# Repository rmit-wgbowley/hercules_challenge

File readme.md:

<!--
Color Palette:
- #F3F4F4
- #0DFDF7
-->

<p align="center">
  
  <br>
  <em>Axial Shake Powered Pill System – Electromechanical Design of the IsoPod by <a href="https://github.com/wgbowley">William Bowley</a></em>
</p>

--- 
The Hercules Challenge is a co-design consortium challenge available to first-semester, first-year engineers through the mandatory introductory class, "Introduction to Professional Engineering."

> [!IMPORTANT]
> `The Pantheon` consortium received a commendation award for their work on the `IsoPod` at the Hercules Challenge night at RMIT.

---

TLDR: Designed, simulated, manufactured, and experimentally validated a human-powered axial electromagnetic generator producing `0.43–0.47 W` from hand shaking using custom FEA and physical prototype testing

# Overview

The `IsoPod` is a pill system that reminds users when to take their medication through an e-ink display on the cylindrical face of the device, providing a simple visual reminder.

This repository focuses on the design, simulation, construction, and validation of the `axial shake generator` (ASG) at the device's core. The generator converts intentional shaking motion into electrical energy via magnetic induction, which charges the IsoPod's Li-Po battery. This extends battery life, or with enough motion, can enable complete self-reliance.

> [!Important]
> **Measured Output (8.8 Hz human shaking):**
> - Peak Voltage: `16.8 V`
> - RMS Voltage: `3.47 V`
> - Power Output: `0.43–0.47 W`

> [!Important]
> The generator has not been tested with a charging load nor power management system. Power output is expected to decrease, but the magnitude is unknown.

### Why generate electrical?

In humanitarian contexts, reliable grid power isn't guaranteed, nor are reliable supply chains for expendable batteries. The ASG decouples the `IsoPod` from external infrastructure by converting user motion into electrical 
energy.

### Table of Contents

- [Overview](#overview)
- [Why generate electrical?](#why-generate-electrical)
- [Axial Shake Generator](#axial-shake-generator)
  - [Electromagnetics](#electromagnetics)
  - [Design & Topology](#design--topology)
  - [Numerical Model](#numerical-model)
  - [Simulation Results](#simulation-results)
- [Construction](#construction)
- [Results](#results)
- [Validation](#validation)
  - [New Mechanical Model](#new-mechanical-model)
  - [Simulation Results](#simulation-results-1)
- [Conclusion](#conclusion)
- [Bibtex Citation](#bibtex-citation)

# Axial Shake Generator

<div align="center">
  
  <p><i>Figure 1: Cross-sectional analysis: <a href="02_fabrication/readme.md">Click here for CAD files</a></i></p>
</div>

The generator consists of an armature `(greyish-olive)` made of poles (magnets), a stator `(minty aqua)` made of slots (coils), and restoring magnets `(light yellow-green)` which act as magnetic springs that allow the armature to build velocity from the user shaking the device with their forearm muscles.

## Electromagnetics

An ASG produces electricity via the interaction between a slot and a pole. When a pole moves axially through a slot, it produces an induced voltage within that slot due to the changing magnetic field generating a changing electric field. The induced electric field opposes the change in magnetic flux that produced it, a consequence of Lenz's law. These ideas come together to form `Faraday's Law of Induction`:

$$V = -N\frac{d\Phi}{dt} \implies -\frac{d\lambda}{dt}$$

where $λ = N\Phi$ is the flux linkage between the slot and pole. Flux linkage can be thought of as the magnitude of how strongly the magnetic field links with the winding (turns in a slot). Higher linkage generally means the system can produce a larger induced voltage for the same change in armature position.

Luckily, using related rates, the two main parameters appear:

$$V_{\text{induced}} = -\frac{d\lambda}{dt} \implies -\frac{d\lambda}{dz} \cdot \frac{dz}{dt}$$

The first term is the derivative of flux linkage over the z-axis (magnetic design), and the second term is the z-axis velocity (mechanical input). These can be analytically approximated as:

> [!important]
> Flux linkage can be approximated analytically for intuition. The final flux linkage was obtained using Finite Element Analysis (FEA).

$$\frac{dz}{dt} = A \omega \cos(\omega t + \phi)$$
$$\frac{d\lambda}{dz} = \frac{d}{dz} (B \cos(kz)) \implies -\mu H k \sin(kz)$$

> [!note]
> For a simple magnetic circuit, magnetic flux density can be related to magnetic field strength by `B = μH`, where `B` is the magnetic flux density, `H` is the magnetic field intensity, and `μ` is the permeability, the ability of a material to support magnetic flux.

where `k = 2π / pitch` is the spatial frequency.

These two derivatives expose the important mechanics of the system. Increasing acceleration `A` and frequency `ω` may increase induced voltage, but these are constrained by the user's physical abilities. Whereas the permeability `μ` and `H` may increase the induced voltage while generally not being constrained by the user's physical abilities.

Once induced voltage is established, the usable electrical power is determined by the generator's internal resistance:

$$P = \frac{V_{\text{rms}}^2}{R_{\text{internal}}}$$

This relationship drives one of the main trade-offs: increasing turns raises induced voltage but also increases resistance due to longer wire length. The optimal design maximizes `V/R`, not just peak voltage.

> [!important]
> The generator design was constrained by the IsoPod system requirements:
> - Cylindrical form factor: radial thickness < `12.5 mm`, height < `250 mm`
> - Human-powered input motion (reasonable frequency and acceleration)
> - Low-maintenance energy harvesting
> - Easy to construct with basic tools

## Design & Topology

<div align="center">
  
  <p><i>Figure 2: High level electrical machine topology</i></p>
</div>

> [!note]
> `N-S` represents an axially magnetized permanent magnet pole. `PA` represents phase A, where `PA+` and `PA-` indicate opposite winding directions.

The high-level topology in figure 2 was selected to enable oscillatory motion through magnetic restoring forces. The end poles act as magnetic springs, creating a restoring force when the armature approaches the limits of travel.

The alternating pole arrangement (`N-S|S-N`) was selected because the transition between opposing poles creates a rapid change in magnetic field along the z-axis, increasing the spatial rate of change of flux linkage:

$$V \propto \frac{d\lambda}{dz}$$

A pole pitch of `10 mm` was selected, matching the pole length and maintaining direct magnetic coupling between adjacent opposing poles. The topology uses four stator slots interacting with four active armature poles, with two additional poles placed on each end of the armature to increase usable travel distance. This allows approximately `20 mm` of positive and negative armature displacement while maintaining magnetic coupling between the armature and stator.

Maintaining slot overlap throughout the motion range produces a more consistent induced voltage waveform, where the primary amplitude is dominated by the mechanical velocity term:

$$V \propto \frac{dz}{dt}$$

The symmetric pole arrangement also reduces unwanted harmonic content compared with asymmetric topologies. Finally, no high-permeability materials were introduced into the armature or stator structure. The stator consists of copper windings, while the magnetic poles use `N52 Neodymium` permanent magnets.

Given the 4 slots within the stator and the 8 poles within the armature, the measured frequency relationship suggests:

$$f_{\text{electrical}} \approx 4 \times f_{\text{mechanical}}$$

This is consistent with the pole pitch and the number of magnetic cycles encountered per mechanical oscillation.

## Numerical Model

> [!important]
> This area is recommended for individuals more familiar with electromagnetic finite element simulations.

The ASG was modelled using `FemmMagneticRender` (FEMM) with `shapely` for translating `PYFEA` CSG (constructive solid geometry) to FEMM native primitives. An axially symmetric coordinate system (z-r) was used due to the generator's rotational symmetry around its z-axis. A Dirichlet boundary condition was applied, with the radial boundary at `2×` the slot outer radius and the axial boundary at `1.2×` the stator tube length. The armature motion relative to the origin was simulated using:

$$ z = \text{travel} \cdot \sin(2\pi f t) $$

The resistance was obtained from `FemmMagneticSolver` during an initial configuration solve, and then the flux linkage was obtained per solve. Using the simulation time-step, the induced voltage was calculated using finite difference:

$$V_{\text{induced}} = -\frac{\lambda_{\text{new}} - \lambda_{\text{old}}}{t_{\text{step}}}$$

This was then used to calculate the RMS voltage, and using the generator's internal resistance, the expected power output was obtained. This method represents a `quasi-transient` method due to its use of asymptotic field conditions ($t=\infty$) per time step. This is reasonable due to the absence of highly magnetically permeable materials and the low operating frequency of the generator.

## Simulation Results

> [!IMPORTANT]
> The model was configured with the following parameters:
> - Temperature: `293.15 K`, Time step: `1ms`
> - Mechanical Shaking Frequency: `8.81 Hz`, Electrical Shaking Frequency: `35.2 Hz`
> - peak-to-peak travel: `40 mm`
> - Pole Coercivity: `956 kA/m`, Pole Permeability: `1.05 ∅`
> - Slot Conductivity: `60.07 MS/m`, Slot Permeability: `1.0 ∅`, Fill Factor: `0.47 ∅`, Turns: `184`

<div align="center">
  
  <p><i>Figure 3: Simulated static |B| along the z-axis of the generator</i></p>
</div>

> [!IMPORTANT]
> The quasi-transient simulation predicted:
> - Time: `0.228 s`, Time steps: `228`
> - Peak voltage: `5.161 V`, RMS Voltage: `2.696 V` 
> - Positive Rate: `486.06 V/s`, Negative Rate: `-844.25 V/s`
> - Resistance: `22.54 Ω`, Power: `0.323 W` 

<div align="center">
  
  <p><i>Figure 4: Simulated induced voltage vs time and position vs time</i></p>
</div>

The parameter file can be found [here](01_simulation/01_simple_motion/parameters.uiv), written in `.uiv` (unit-informed values). The simulation files can be found [here](01_simulation/readme.md), written in Python using the `pyfea` solver-adapter engine. Solver assumptions can be found [here](03_data/assumptions_printout.md).

## Construction

The generator was printed out of ABS on a Voron 2.4. The armature consisted of a carbon fibre rod with `8` x `N52` poles inserted into it in the pattern described above, using superglue to secure the end poles.

The stator consisted of `4` coils with `180` turns per coil of `0.2 mm` enameled copper wire, with each coil wound in the opposite direction to the last as described above. The coils were secured in place with `10 mm` and `5 mm` thick Kapton tape, with the first and last layers of the coil being wrapped.

The restoring magnets were flat `12 mm x 3 mm` neodymium magnets. The generator stator was split into two pieces: the main piece, which housed the coils and one restoring magnet, and the cap, which held the other restoring magnet and was attached via `3` x `M3 x 20 mm` bolts. The two outputs of the generator were secured to the side and then extended with `~1.25 mm` stranded copper wire.

<div align="center">
  
  <p><i>Figure 5: Side profile (Construction)</i></p>
</div>

## Results

The completed generator was tested by hand-shaking at a measured fundamental mechanical frequency of `8.81 Hz` with an electrical frequency of `35.2 Hz`
(the 4 coils produce 4 cycles per mechanical oscillation). The open-circuit voltage was recorded using an oscilloscope:

> [!IMPORTANT]
> The oscilloscope measurements:
> - Positive Peak: `16.8 V`, Negative Peak: `-16.4 V`
> - Positive Rate: `131 V/s`, Negative Rate: `-246 V/s` (Slew Rate)
> - V_RMS(AV): `3.47 V`, V_RMS(PEAK): `3.63 V`
> - Resistance: `27.8 Ω`, Power: `0.43-0.47 W`

> [!NOTE]
> Slew rate can be affected by probe loading due to parasitic capacitance and inductance. Hence `dv/dt` may be slowed due to the `RLC` circuit formed.

<div align="center">
  
  <p><i>Figure 6: Voltage vs time trace @ 10V/div vertical, 50ms/div horizontal</i></p>
</div>

The measured waveform shown in Figure 6 has a similar shape to the predicted waveform in Figure 4 but seems less periodic and more jerky. Another observation is that the negative recovery appears stretched while still being a similar amplitude. This is most likely attributed to degradation of the prototype due to its usage as a demo item.

# Validation

The simulated power output was `0.323 W` whereas the measured power was `0.43-0.47 W`, which is `25-45%` lower than the measured value. The peak voltages are much higher and the slew rate was significantly different, leading to the possible source being the idealized motion of the armature versus the realized motion.

The simulation used the same mechanical frequency but produced lower peak voltages. If the prototype's armature acceleration was much higher than expected, the armature was likely slamming into the end-caps due to the repulsion force not being high enough. The maximum velocity was most likely higher and hence:

$$V \propto \frac{d\lambda}{dz}$$

## New Mechanical Model

> [!important]
> This area is recommended for individuals more familiar with electromagnetic finite element simulations.

Given this, a new model for the motion could be proposed that takes into consideration the magnetic repulsion force and the likely much higher mechanical acceleration but lower frequency, using an oscillating force function:

$$F_{\text{magnetic}} = -\frac{dU}{dz}$$
$$F_{\text{shaking}} = am\sin(\omega t + \phi)$$

One approach would be to model the armature velocity as:

$$\frac{dz}{dt} = \int \frac{F_{\text{magnetic}} + F_{\text{shaking}}}{m} \ dt$$

> [!Note]
> Euler method was used to integrate from acceleration to z-position, the stability was not formalized.

However, given the ability of `FemmMagneticSolver` to calculate the Maxwell stress tensor, the $F_{\text{magnetic}}$ term was obtained directly from the solver rather than using finite difference of the magnetic energy density over the z-axis. This decouples the solution from the displacement output, removing dynamic step sizes and leading to a potentially more stable solution.

## Simulation Results 

> [!IMPORTANT]
> The model was configured with the following parameters:
> - Temperature: `293.15 K`, Time step: `1 ms`
> - Mechanical Shaking Frequency: `8.8 Hz`, Electrical Shaking Frequency: `35.2 Hz`
> - Acceleration: `100 m/s²`, peak-to-peak travel: `40 mm`
> - Pole Coercivity: `956 kA/m`, Pole Permeability: `1.05 ∅`
> - Slot Conductivity: `60.07 MS/m`, Slot Permeability: `1.0 ∅`, Fill Factor: `0.47 ∅`, Turns: `184`

> [!IMPORTANT]
> The quasi-transient simulation predicted:
> - Time: `0.228 s`, Time steps: `228`
> - Peak voltage: `12.35 V`, RMS Voltage: `3.44 V` 
> - Positive Rate: `634.76 V/s`, Negative Rate: `-2.32 kV/s`
> - Resistance: `22.54 Ω`, Power: `0.526 W` 

<div align="center">
  
  <p><i>Figure 7: New simulation results (Simulation Results)</i></p>
</div>

The parameter file can be found [here](01_simulation/02_advance_motion/parameters.uiv), written in `.uiv` (unit-informed values). The simulation files can be found [here](01_simulation/readme.md), written in Python using the `pyfea` solver-adapter engine. Solver assumptions can be found [here](03_data/assumptions_printout.md).

# Conclusion

The axial shake generator successfully produced `0.43-0.47 W` of usable power from human motion at a mechanical frequency of `8.8 Hz` (electrical `35.2 Hz`) with an unknown acceleration function. The simulation with the new mechanical model predicted `0.526 W`, within `12-22%` of measured values. The differences in slew rates between the simulation and measured results can be attributed to no-load electrical dynamics versus the oscilloscope probe loading.

> [!IMPORTANT]
> Key Takeaways:
> - The `N-S|S-N` magnet topology effectively increases `dλ/dz`, producing sharp B-field spikes
> - The mechanical model incorporating boundary clamping and Maxwell stress tensor produces a waveform shape much closer to reality than the ideal sinusoidal model
> - The quasi-transient model using a hybrid force function predicted power within `22%`; however, acceleration needs validation
> - The `180` turn prototype produced `16.8 V` peaks, which is sufficient for the IsoPod's target applications

> [!TIP]
> Future work should focus on:
> - Using a shaking apparatus for repeatable external motion paths that could be fed into the simulation
> - Improving fill factor to decrease generator size or increase the number of turns within the generator's form factor
> - Validating the computational model across more generator parameters and pole-slot factors
> - Investigating whether the end-cap magnets improve energy output or reduce it
> - Investigating efficient methods of converting electrical energy into stored energy
> - Investigating the effect of the probe's `RLC` circuit or generator conversion circuit on dynamics

The generator design demonstrated the feasibility of powering low-energy devices in humanitarian contexts where grid power is unreliable, depending on load factors. However, it may be more viable as a battery supplementary system, depending on the trade-offs between battery size and generator duty cycle.

### Bibtex Citation:

```
@misc{Bowley_2024,
  author = {Bowley, William},
  title = {{IsoPod: Axial Shake Generator}},
  url = {https://github.com/rmit-wgbowley/isopod-generator},
  year = {2024},
  note = {
    GitHub repository,
    Electromagnetic Subsystem Of The Isopod
  },
  license = {MIT}
}
```

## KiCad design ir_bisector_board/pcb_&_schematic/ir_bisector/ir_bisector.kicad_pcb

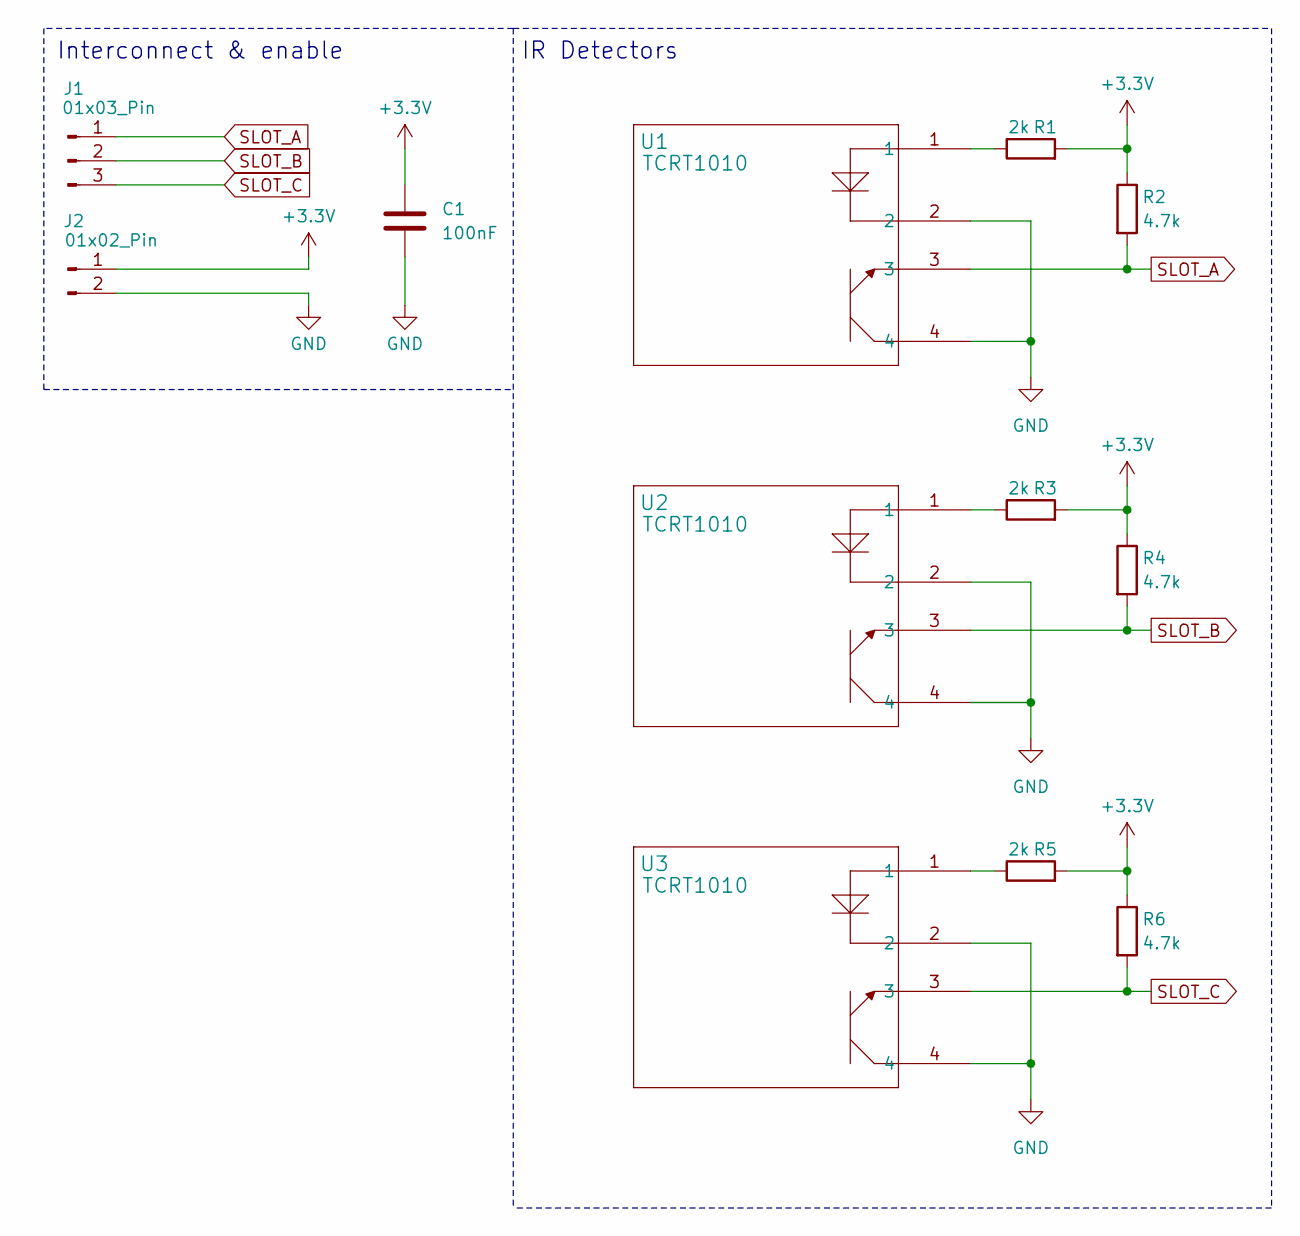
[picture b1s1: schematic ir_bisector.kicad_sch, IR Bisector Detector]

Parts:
C1: 100nF; C_0603_1608Metric
J1: 01x03_Pin; PinHeader_1x03_P1.00mm_Vertical
J2: 01x02_Pin; PinHeader_1x02_P1.00mm_Vertical
R1, R3, R5: 2k; R_0603_1608Metric
R2, R4, R6: 4.7k; R_0603_1608Metric
U1, U2, U3: TCRT1010; TCRT1010_VIS

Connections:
+3.3V: C1.1, J2.1, R1.2, R2.1, R3.2, R4.1, R5.2, R6.1
GND: C1.2, J2.2, U1.2, U1.4, U2.2, U2.4, U3.2, U3.4
unnamed: R1.1, U1.1
unnamed: R3.1, U2.1
unnamed: R5.1, U3.1
SLOT_A: J1.1, R2.2, U1.3
SLOT_B: J1.2, R4.2, U2.3
SLOT_C: J1.3, R6.2, U3.3

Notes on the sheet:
Interconnect & enable
IR Detectors

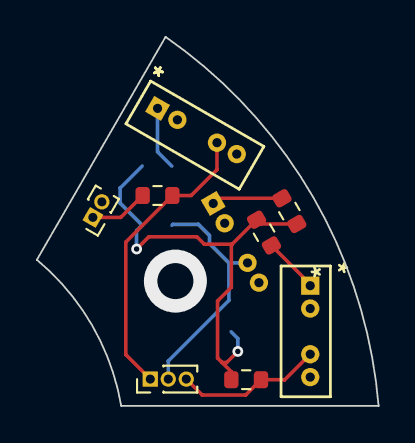
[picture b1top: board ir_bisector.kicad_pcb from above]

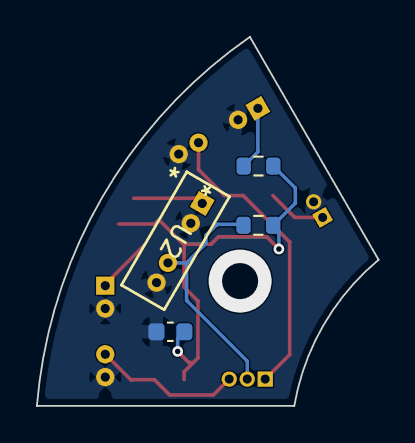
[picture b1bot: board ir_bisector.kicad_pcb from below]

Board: 2 copper layers, 19.0 x 20.5 mm, 12 parts (4 on the bottom side), 8 nets.

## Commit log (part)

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2026-05-19 rough modelling before FEM of generator.
2026-05-21 Final updates to rough model before making FEM model
2026-05-21 WIP Save: Static simulation working -> Moving to basic dynamic
2026-05-21 generator - dynamic works
2026-05-22 more plots of axial-shake generator simulation
2026-05-24 WIP: IR Bisector PCB
2026-05-24 sensor board finished
2026-05-26 Add MIT License to the project
2026-05-26 final commit.
2026-06-01 Moving submission prototype into proposal_submission
2026-06-01 Including modelling assumptions & relocating submission images
2026-06-01 HTML corrections to figure layout
2026-06-04 demonstrator team meeting notes
2026-06-07 resonant frequency model for springs
2026-06-08 Demonstration generator code & images
2026-06-12 rework before deliverable prototype for competition night
2026-06-16 Updates to readme & descoping deliverable pcb
2026-06-16 Correction (Formatting)*
2026-06-18 final commit (hopefully) - thanks guys
2026-06-26 Quick Save -> Reorganization
2026-06-27 adding images & data
2026-06-27 new folder/file structure based on 01,02,...,n
2026-06-27 Look of the new start of the readme within the repo
2026-06-27 what about with power in it like that?
2026-06-27 okay hows that?
2026-06-27 correction
2026-06-27 check + add side profile image.
2026-06-27 introduction
2026-06-27 test with electromagnetic section
2026-06-27 finished electromagnetics area
2026-06-27 few fixes
2026-06-27 test
2026-06-27 Going to use the correct arrows: "→"
2026-06-27 space update
2026-06-27 decreasing the spacing between the pieces
2026-06-27 switched to an image.
2026-06-27 UPDATED IMAGE
2026-06-27 Upto simulation now
2026-06-27 improvements to readme
2026-06-28 fixed the error in the figures -> 6 poles to the correct 8 poles
2026-06-28 remove note
2026-06-28 numerical model section
2026-06-28 added data & graph
2026-06-28 simulation section start
2026-06-28 simulation section
2026-06-28 construction section
2026-06-28 results section
2026-06-28 new model path
2026-06-28 updates moving the fem into simple motion to make the new one using more complex dynamics
2026-06-28 new model
2026-06-28 first draft.
2026-06-28 final commit
2026-06-28 Merge development into main for release (#10)
    * Quick Save -> Reorganization
    * adding images & data
    * new folder/file structure based on 01,02,...,n
    * Create readme.md
    * Look of the new start of the readme within the repo
    * what about with power in it like that?
2026-06-29 Proofreading Edits
2026-06-29 Final edits

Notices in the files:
readme.md:
Bibtex Citation::
@misc{Bowley_2024,
author = {Bowley, William},
title = {{IsoPod: Axial Shake Generator}},
url = {https://github.com/rmit-wgbowley/isopod-generator},
year = {2024},
note = {
GitHub repository,
Electromagnetic Subsystem Of The Isopod
license = {MIT}
